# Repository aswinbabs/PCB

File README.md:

## PCB_Designs

```plaintext
├── PCB_SCH/
│   ├── LED.sch
│   ├── LED_5.sch
│   ├── LED_10.sch
│   ├── Timer.sch
│   ├── Transistor_ckt.sch
│   ├── Two_stage_amp.sch
│   ├── LED_WITH_8051.sch
│   └── LCD_16x2_with_8051.sch
├── PCB_BRD/
│   ├── LED.brd
│   ├── LED_5.brd
│   ├── LED_10.brd
│   ├── Timer.brd
│   ├── Transistor_ckt.brd
│   ├── Two_stage_amp.brd
│   ├── LED_WITH_8051.brd
│   └── LCD_16x2_with_8051.brd
└── README.md

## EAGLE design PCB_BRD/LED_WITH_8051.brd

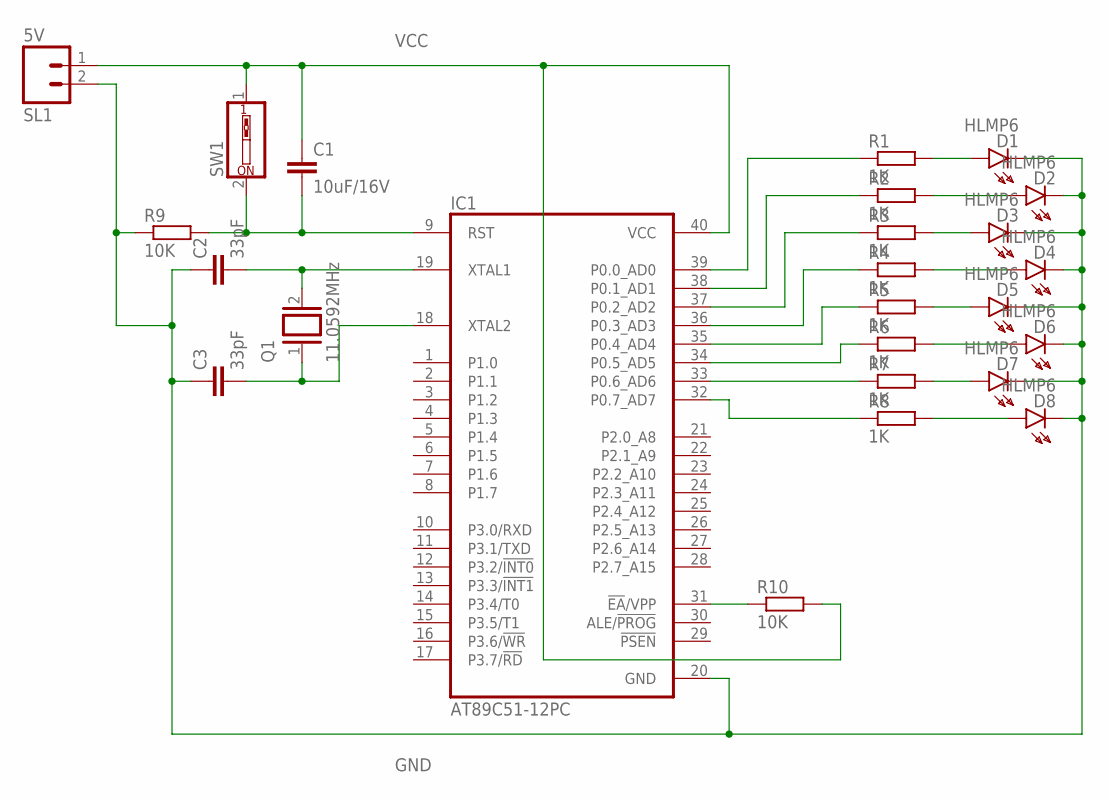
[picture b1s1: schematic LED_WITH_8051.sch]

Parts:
C1: 10uF/16V; C025-025X050
C2, C3: 33pF; C025-025X050
D1, D2, D3, D4, D5, D6, D7, D8: HLMP6
IC1: AT89C51-12PC; DIL40
Q1: 11.0592MHz; Q
R1, R2, R3, R4, R5, R6, R7, R8: 1K; 0204/7
R9, R10: 10K; 0204/7
SL1: 5V; 02P
SW1: SW_DIP-1; EDG-01

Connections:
GND: C2.1, C3.1, D1.K, D2.K, D3.K, D4.K, D5.K, D6.K, D7.K, D8.K, IC1.20 (GND), R9.1, SL1.2
unnamed: C2.2, IC1.19 (XTAL1), Q1.2
unnamed: C3.2, IC1.18 (XTAL2), Q1.1
unnamed: IC1.36 (P0.3_AD3), R4.1
unnamed: C1.2, IC1.9 (RST), R9.2, SW1.2
unnamed: D1.A, R1.2
unnamed: D2.A, R2.2
unnamed: D3.A, R3.2
unnamed: D4.A, R4.2
unnamed: D5.A, R5.2
unnamed: D6.A, R6.2
unnamed: D7.A, R7.2
unnamed: D8.A, R8.2
unnamed: IC1.39 (P0.0_AD0), R1.1
unnamed: IC1.38 (P0.1_AD1), R2.1
unnamed: IC1.32 (P0.7_AD7), R8.1
unnamed: IC1.33 (P0.6_AD6), R7.1
unnamed: IC1.37 (P0.2_AD2), R3.1
unnamed: IC1.35 (P0.4_AD4), R5.1
unnamed: IC1.34 (P0.5_AD5), R6.1
unnamed: IC1.31 (!EA!/VPP), R10.1
VCC: C1.1, IC1.40 (VCC), R10.2, SL1.1, SW1.1

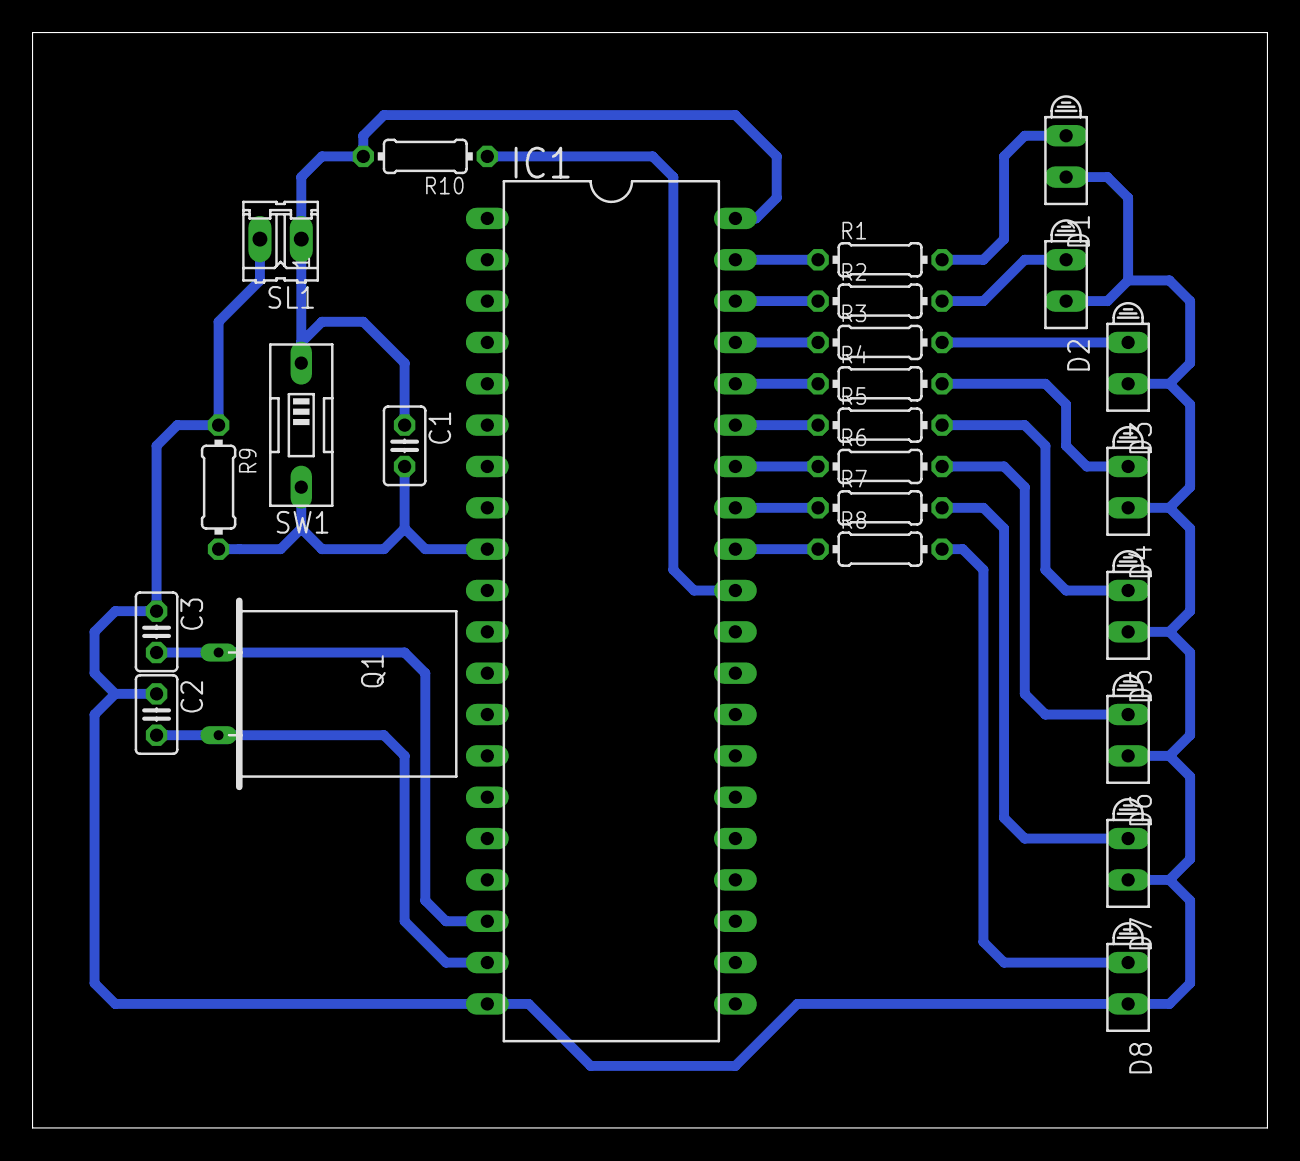
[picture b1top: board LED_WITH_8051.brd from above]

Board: 2 copper layers, 75.9 x 67.3 mm, 25 parts (0 on the bottom side), 22 nets.

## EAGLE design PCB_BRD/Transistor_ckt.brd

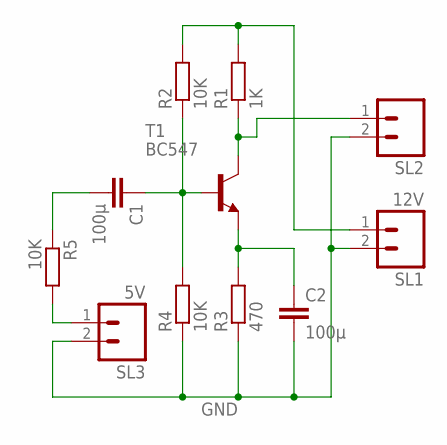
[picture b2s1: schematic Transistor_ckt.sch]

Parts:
C1, C2: 100µ; C025-025X050
R1: 1K; 0204/7
R2, R4, R5: 10K; 0204/7
R3: 470; 0204/7
SL1: 12V; 02P
SL2: M02; 02P
SL3: 5V; 02P
T1: BC547; TO92

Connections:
GND: C2.2, R3.1, R4.1, SL1.2, SL2.2, SL3.2
unnamed: R1.2, R2.2, SL1.1
unnamed: R1.1, SL2.1, T1.3 (C)
unnamed: C2.1, R3.2, T1.1 (E)
unnamed: C1.2, R5.1
unnamed: C1.1, R2.1, R4.2, T1.2 (B)
unnamed: R5.2, SL3.1

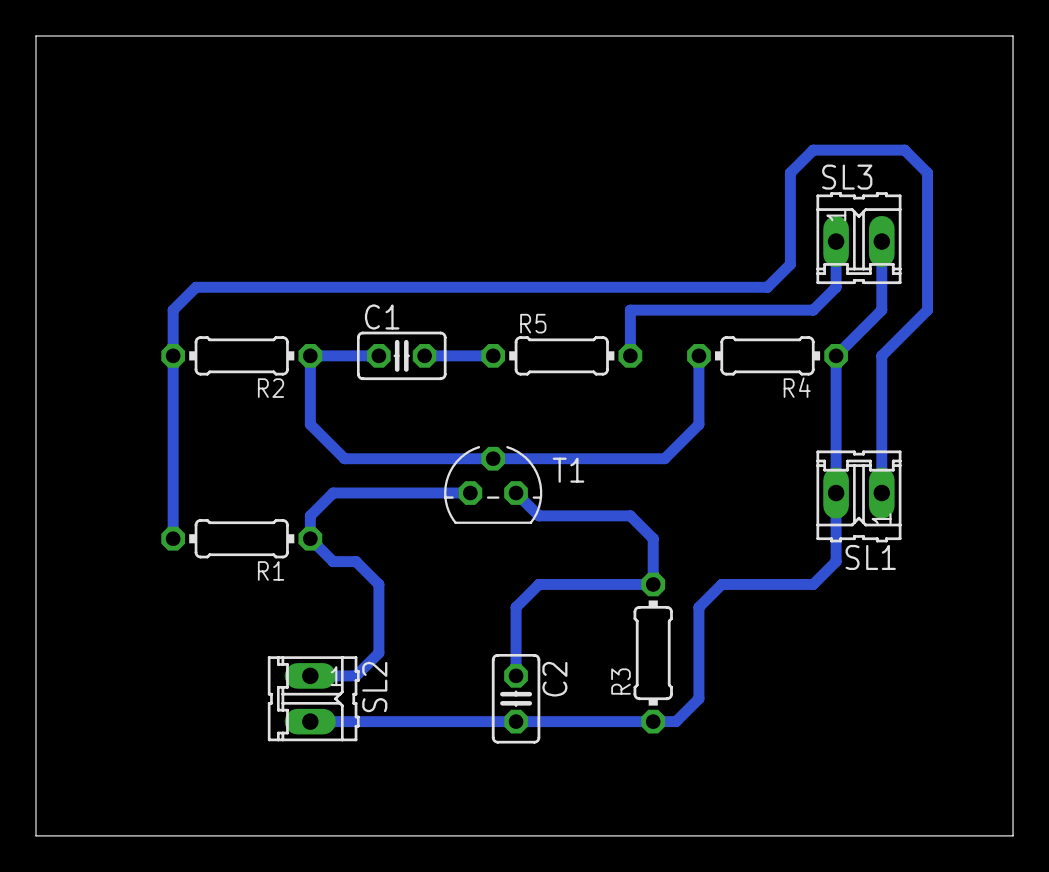
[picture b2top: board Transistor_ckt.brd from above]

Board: 2 copper layers, 54.3 x 44.4 mm, 11 parts (0 on the bottom side), 7 nets.

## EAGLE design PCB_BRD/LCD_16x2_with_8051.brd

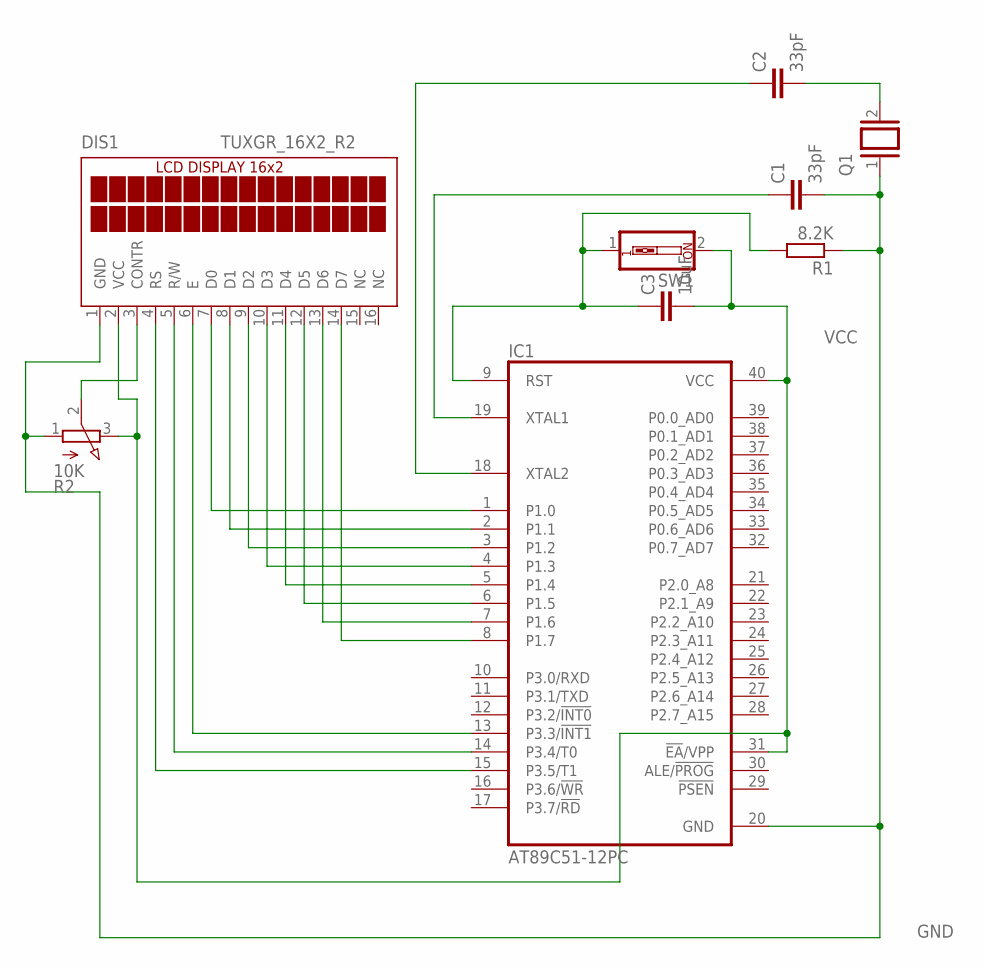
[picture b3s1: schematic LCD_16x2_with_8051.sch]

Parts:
C1, C2: 33pF; C025-025X050
C3: 10uF; C025-025X050
DIS1: TUXGR_16X2_R2
IC1: AT89C51-12PC; DIL40
Q1: XTAL; Q
R1: 8.2K; 0204/7
R2: 10K; 3RP/1610N
SW1: SW_DIP-1; EDG-01

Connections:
GND: C1.2, DIS1.1 (GND), IC1.20 (GND), Q1.1, R1.1, R2.1 (A)
unnamed: DIS1.7 (D0), IC1.1 (P1.0)
unnamed: DIS1.8 (D1), IC1.2 (P1.1)
unnamed: DIS1.9 (D2), IC1.3 (P1.2)
unnamed: DIS1.10 (D3), IC1.4 (P1.3)
unnamed: DIS1.11 (D4), IC1.5 (P1.4)
unnamed: DIS1.12 (D5), IC1.6 (P1.5)
unnamed: DIS1.13 (D6), IC1.7 (P1.6)
unnamed: DIS1.14 (D7), IC1.8 (P1.7)
unnamed: DIS1.6 (E), IC1.13 (P3.3/!INT1)
unnamed: DIS1.5 (R/W), IC1.14 (P3.4/T0)
unnamed: DIS1.4 (RS), IC1.15 (P3.5/T1)
unnamed: DIS1.3 (CONTR), R2.2 (S)
unnamed: C3.1, IC1.9 (RST), R1.2, SW1.1
unnamed: C2.1, IC1.18 (XTAL2)
unnamed: C1.1, IC1.19 (XTAL1)
unnamed: C2.2, Q1.2
VCC: C3.2, DIS1.2 (VCC), IC1.31 (!EA!/VPP), IC1.40 (VCC), R2.3 (E), SW1.2

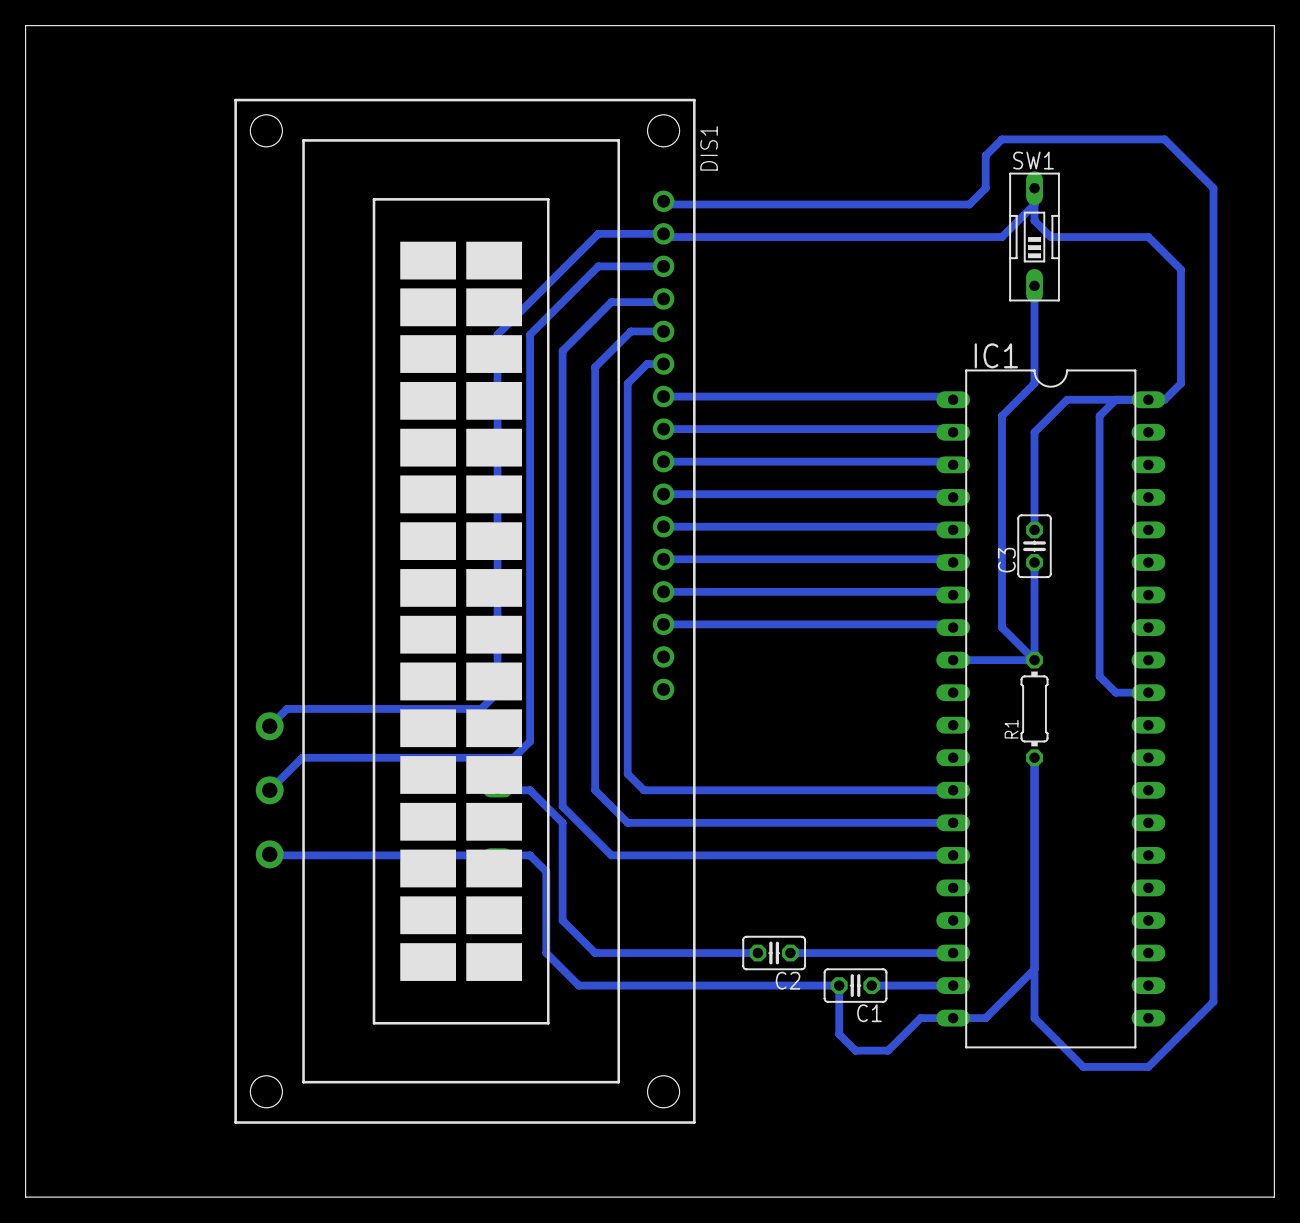
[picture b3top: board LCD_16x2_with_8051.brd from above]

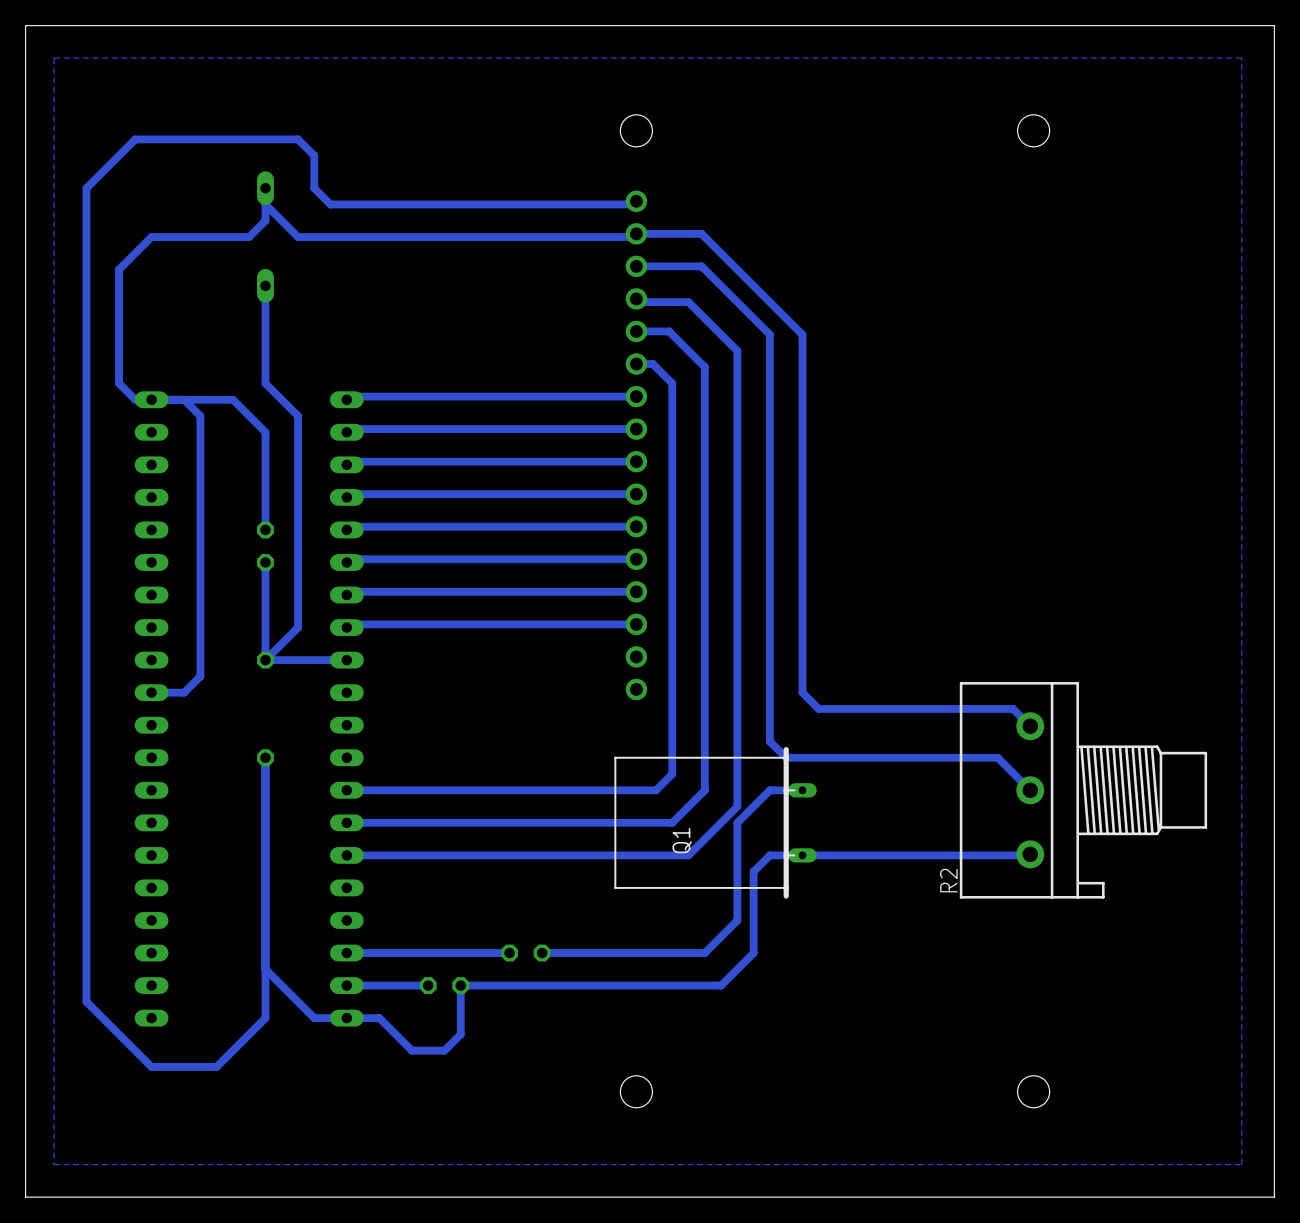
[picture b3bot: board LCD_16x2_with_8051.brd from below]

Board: 2 copper layers, 97.5 x 91.4 mm, 9 parts (2 on the bottom side), 18 nets.

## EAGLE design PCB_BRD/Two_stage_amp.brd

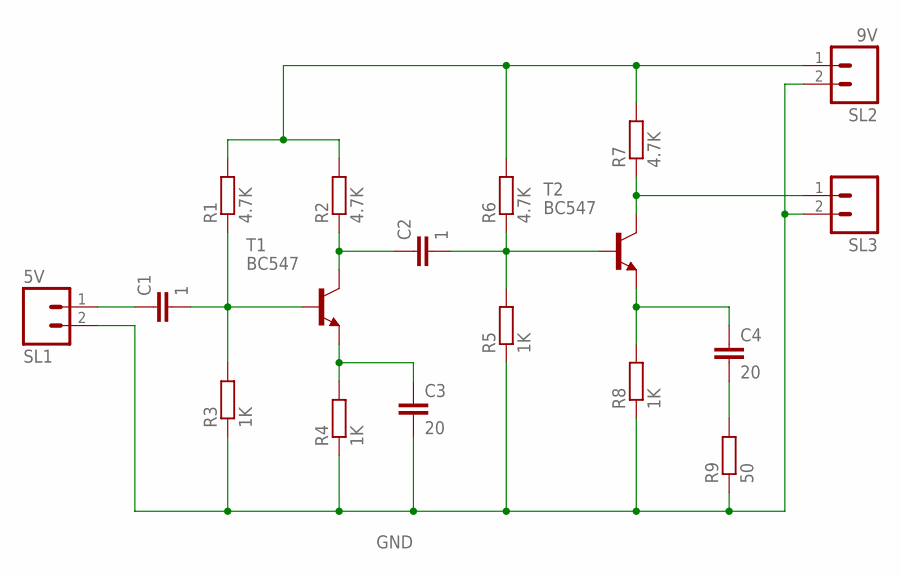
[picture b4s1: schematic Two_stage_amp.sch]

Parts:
C1, C2: 1; C025-025X050
C3, C4: 20; C025-025X050
R1, R2, R6, R7: 4.7K; 0204/7
R3, R4, R5, R8: 1K; 0204/7
R9: 50; 0204/7
SL1: 5V; 02P
SL2: 9V; 02P
SL3: M02; 02P
T1, T2: BC547; TO92

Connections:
GND: C3.2, R3.1, R4.1, R5.1, R8.1, R9.1, SL1.2, SL2.2, SL3.2
unnamed: C1.2, R1.1, R3.2, T1.2 (B)
unnamed: C2.1, R2.1, T1.3 (C)
unnamed: C1.1, SL1.1
unnamed: C2.2, R5.2, R6.1, T2.2 (B)
unnamed: R1.2, R2.2, R6.2, R7.2, SL2.1
unnamed: R7.1, SL3.1, T2.3 (C)
unnamed: C4.1, R8.2, T2.1 (E)
unnamed: C3.1, R4.2, T1.1 (E)
unnamed: C4.2, R9.2

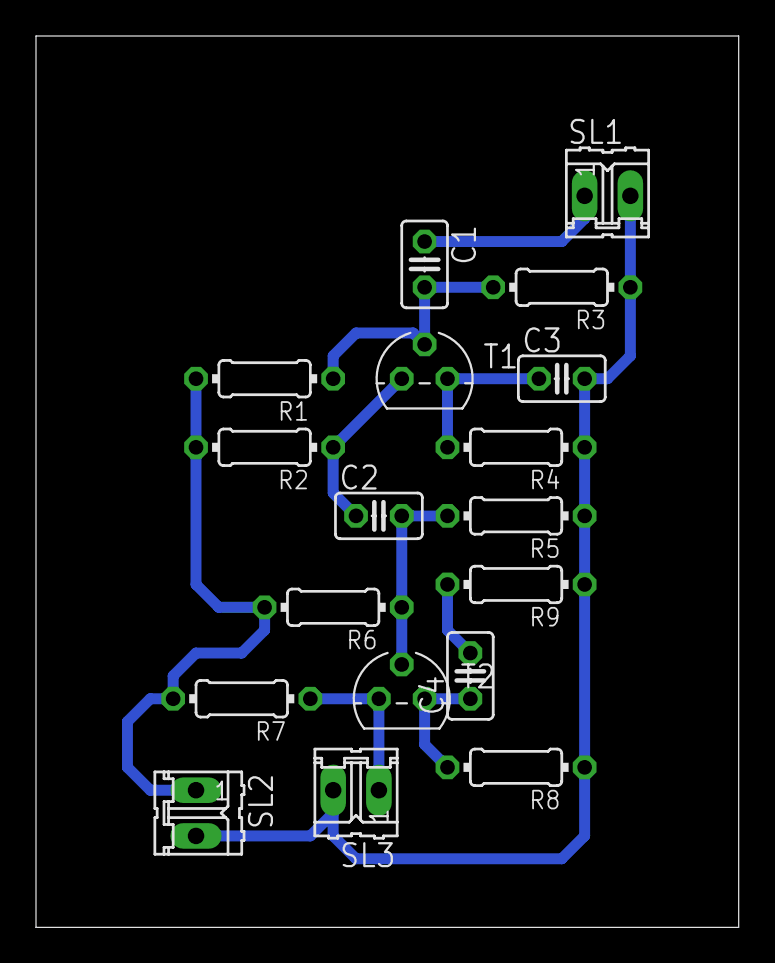
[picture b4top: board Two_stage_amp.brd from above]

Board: 2 copper layers, 39.0 x 49.5 mm, 18 parts (0 on the bottom side), 10 nets.

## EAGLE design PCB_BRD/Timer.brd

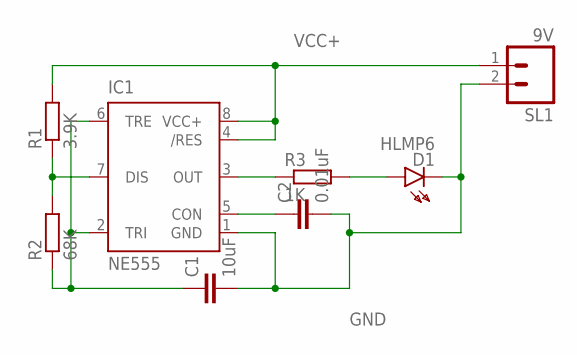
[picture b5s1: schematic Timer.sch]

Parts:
C1: 10uF; C025-025X050
C2: 0.01uF; C025-025X050
D1: HLMP6
IC1: NE555; DIL-08
R1: 3.9K; 0204/7
R2: 68K; 0204/7
R3: 1K; 0204/7
SL1: 9V; 02P

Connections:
GND: C1.2, C2.2, D1.K, IC1.1 (GND), SL1.2
unnamed: C1.1, IC1.2 (TRI), IC1.6 (TRE), R2.1
unnamed: IC1.7 (DIS), R1.1, R2.2
unnamed: C2.1, IC1.5 (CON)
unnamed: IC1.3 (OUT), R3.1
unnamed: D1.A, R3.2
VCC+: IC1.4 (/RES), IC1.8 (VCC+), R1.2, SL1.1

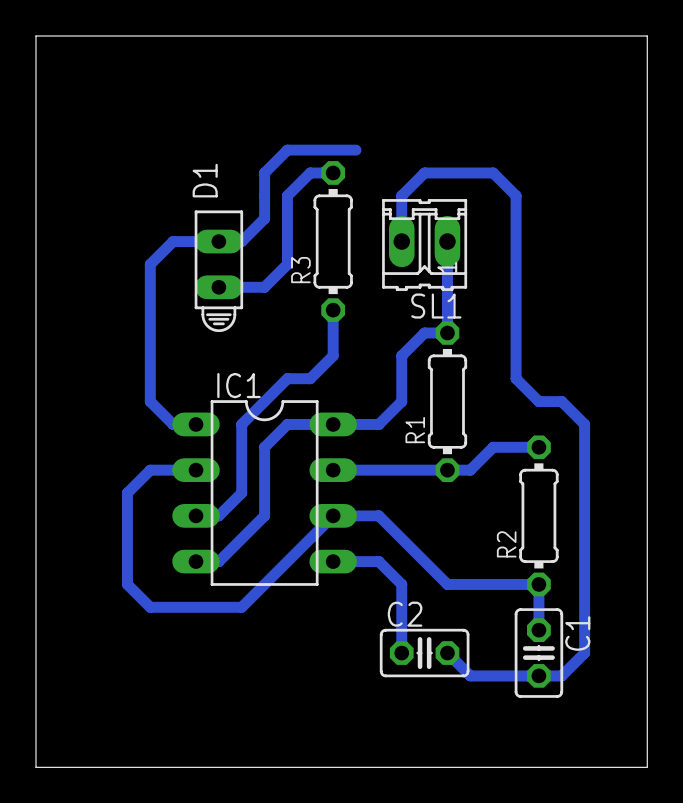
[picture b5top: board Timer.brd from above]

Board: 2 copper layers, 34.0 x 40.6 mm, 8 parts (0 on the bottom side), 7 nets.
